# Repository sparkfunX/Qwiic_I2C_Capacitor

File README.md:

SparkFun Qwiic Digital Capacitor
=============================

[*SparkFun Qwiic Digital Capacitor NCD2400M (SPX- 17182)*](https://www.sparkfun.com/products/17182) 

Ever need to fine tune an oscillator circuit or RF filter? It can be tricky and repetitive switching out capacitors on a PCB. The Qwiic Digital Capacitor, complete with the NCD2400M IC, can be a great solution. Solder the nibs onto any 0603 or 0402 footprint, plug in a Qwiic cable and RedBoard, and change the capacitance in code.

Repository Contents
-------------------

* **/Documents** - Datasheet for the NCD2400M IC.
* **/Hardware** - Eagle design files (.brd, .sch).
* **/Production** - Production panel files (.brd).

Documentation
-------------
* **[Arduino Library](https://github.com/sparkfun/SparkFun_Qwiic_Digital_Capacitor_Arduino_Library)** - Arduino library for the SparkFun Qwiic Digital Capacitor - NCD2400M.

License Information
-------------------

This product is _**open source**_!

Please review the LICENSE.md file for license information.

If you have any questions or concerns regarding our licensing, please contact technical support on our [SparkFun Forum](https://www.sparkfun.com/viewforum.php?f=152).

Distributed as-is; no warranty is given.

- Your friends at SparkFun

_<COLLABORATION CREDIT>_

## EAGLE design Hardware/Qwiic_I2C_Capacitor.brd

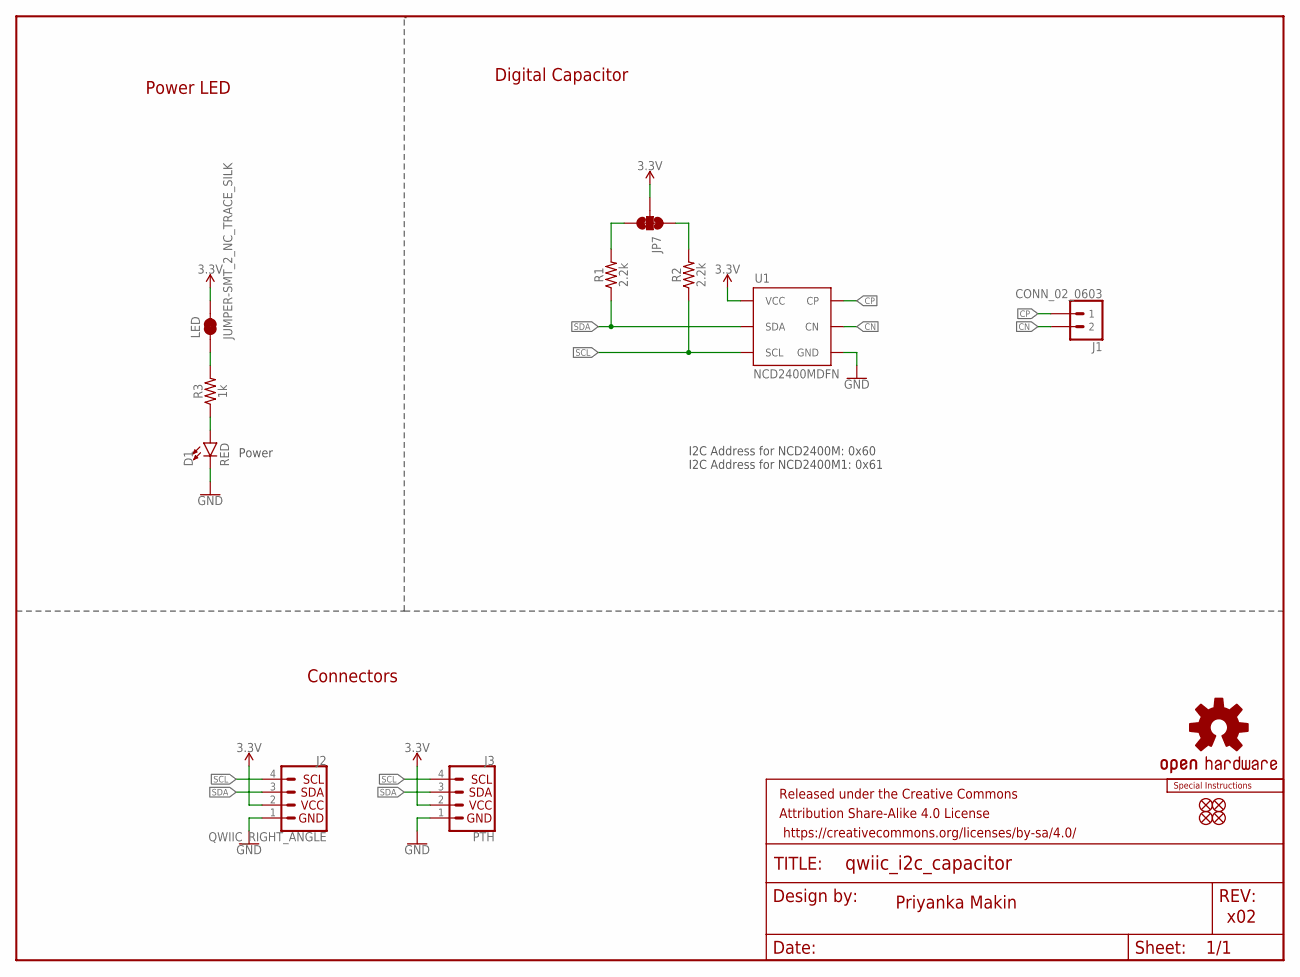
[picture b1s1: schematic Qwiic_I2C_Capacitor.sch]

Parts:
D1: RED; LED-0603
FRAME1: FRAME-LETTER; CREATIVE_COMMONS
J1: CONN_02_0603; 0603_CASTELLATED
J2: QWIIC_RIGHT_ANGLE; JST04_1MM_RA
J3: PTH; 1X04_NO_SILK
JP1, JP2, JP5, JP6: FIDUCIAL0.2MM; FIDUCIAL-0.2MM
JP7: JUMPER-SMT_3_2-NC_TRACE_SILK; SMT-JUMPER_3_2-NC_TRACE_SILK
LED: JUMPER-SMT_2_NC_TRACE_SILK; SMT-JUMPER_2_NC_TRACE_SILK
LOGO1: OSHW-LOGOMINI; OSHW-LOGO-MINI
LOGO2: SPECIAL_INSTRUCTIONS-ORDERING; ORDERING_INSTRUCTIONS
R1, R2: 2.2k; 0603
R3: 1k; 0603
U1: NCD2400MDFN; DFN6

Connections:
3.3V: J2.2, J3.2 (VCC), JP7.2, LED.2, U1.4 (VCC)
CN: J1.2, U1.3 (CN)
CP: J1.1, U1.2 (CP)
GND: D1.C, J2.1, J3.1 (GND), U1.5 (GND)
unnamed: JP7.3, R1.2
unnamed: JP7.1, R2.2
unnamed: D1.A, R3.1
unnamed: LED.1, R3.2
SCL: J2.4, J3.4 (SCL), R2.1, U1.6 (SCL)
SDA: J2.3, J3.3 (SDA), R1.1, U1.1 (SDA)

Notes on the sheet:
x02
Power
Connectors
Priyanka Makin
I2C Address for NCD2400M: 0x60 I2C Address for NCD2400M1: 0x61
Digital Capacitor
Power LED

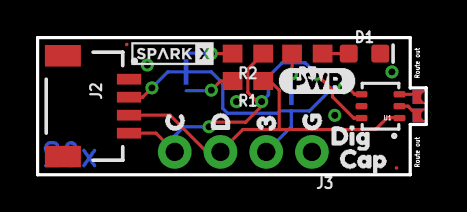
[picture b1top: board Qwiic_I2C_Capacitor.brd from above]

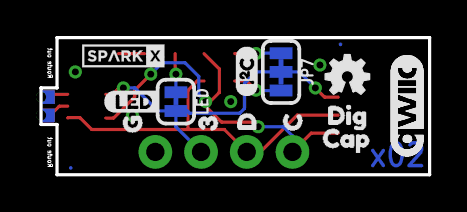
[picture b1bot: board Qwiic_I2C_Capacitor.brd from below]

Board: 2 copper layers, 21.6 x 7.6 mm, 36 parts (16 on the bottom side), 10 nets.

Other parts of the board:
U$1: PWR2
U$3, U$7: 32
U$4, U$8: C0
U$5, U$13: D1
U$6, U$14: G3
U$9: I_SUPER2_C-()-03
U$11, U$18: CAP1
U$12, U$16: SPARKX-TINY
U$15: LED0
U$20, U$21: QWIIC_COPYRIGHT_SMALL
U$22, U$23: DIG0

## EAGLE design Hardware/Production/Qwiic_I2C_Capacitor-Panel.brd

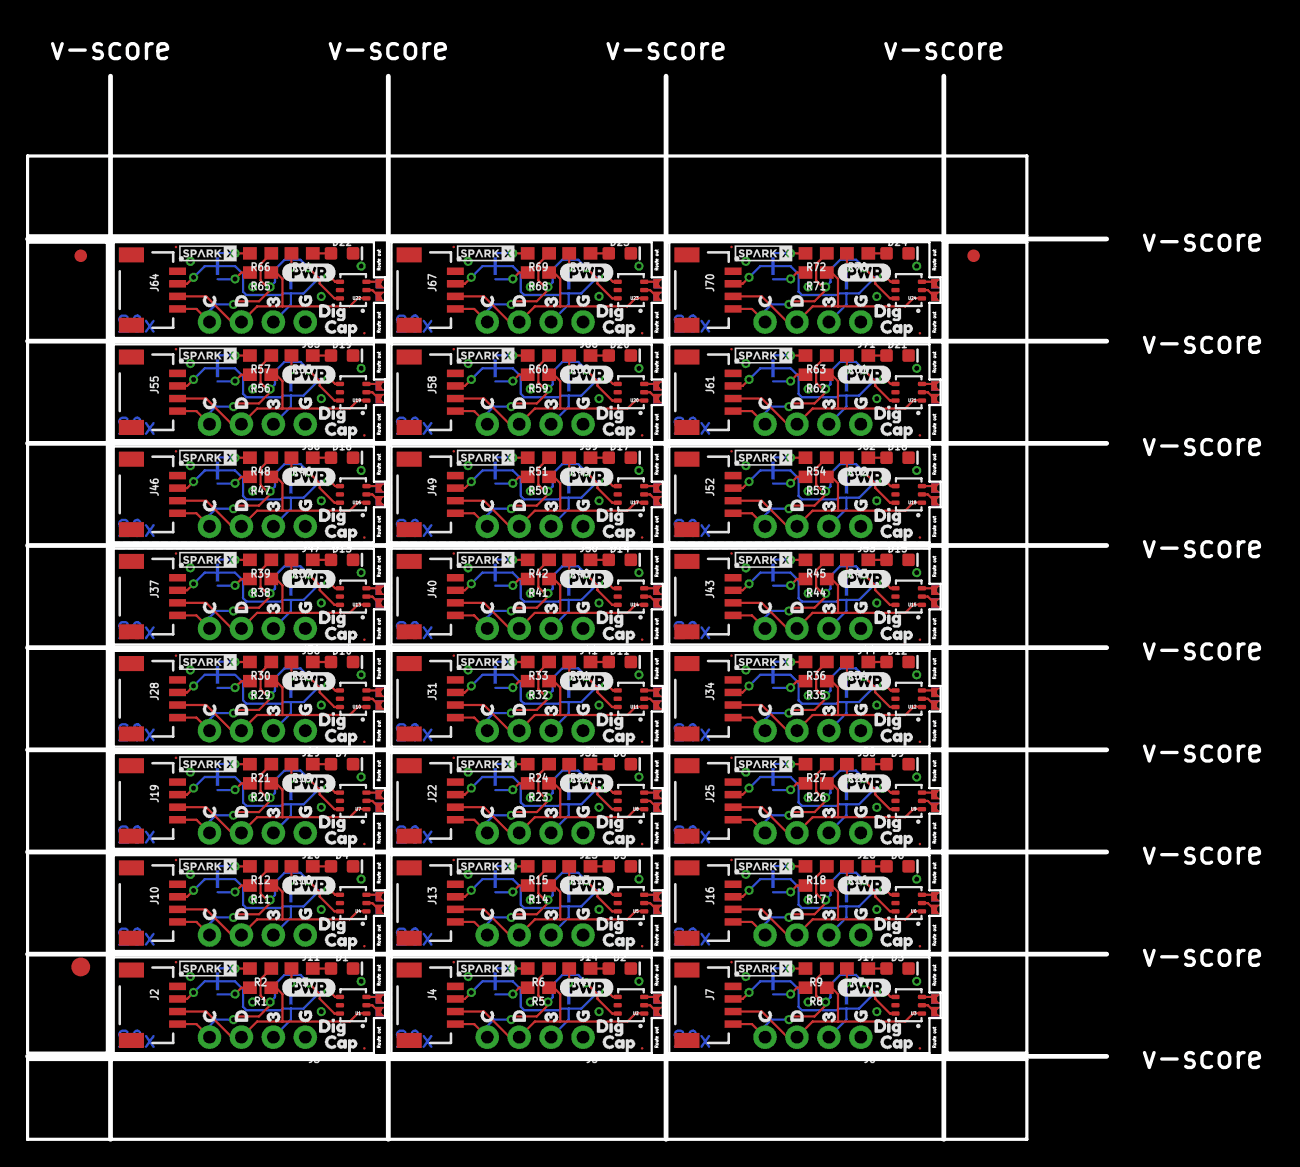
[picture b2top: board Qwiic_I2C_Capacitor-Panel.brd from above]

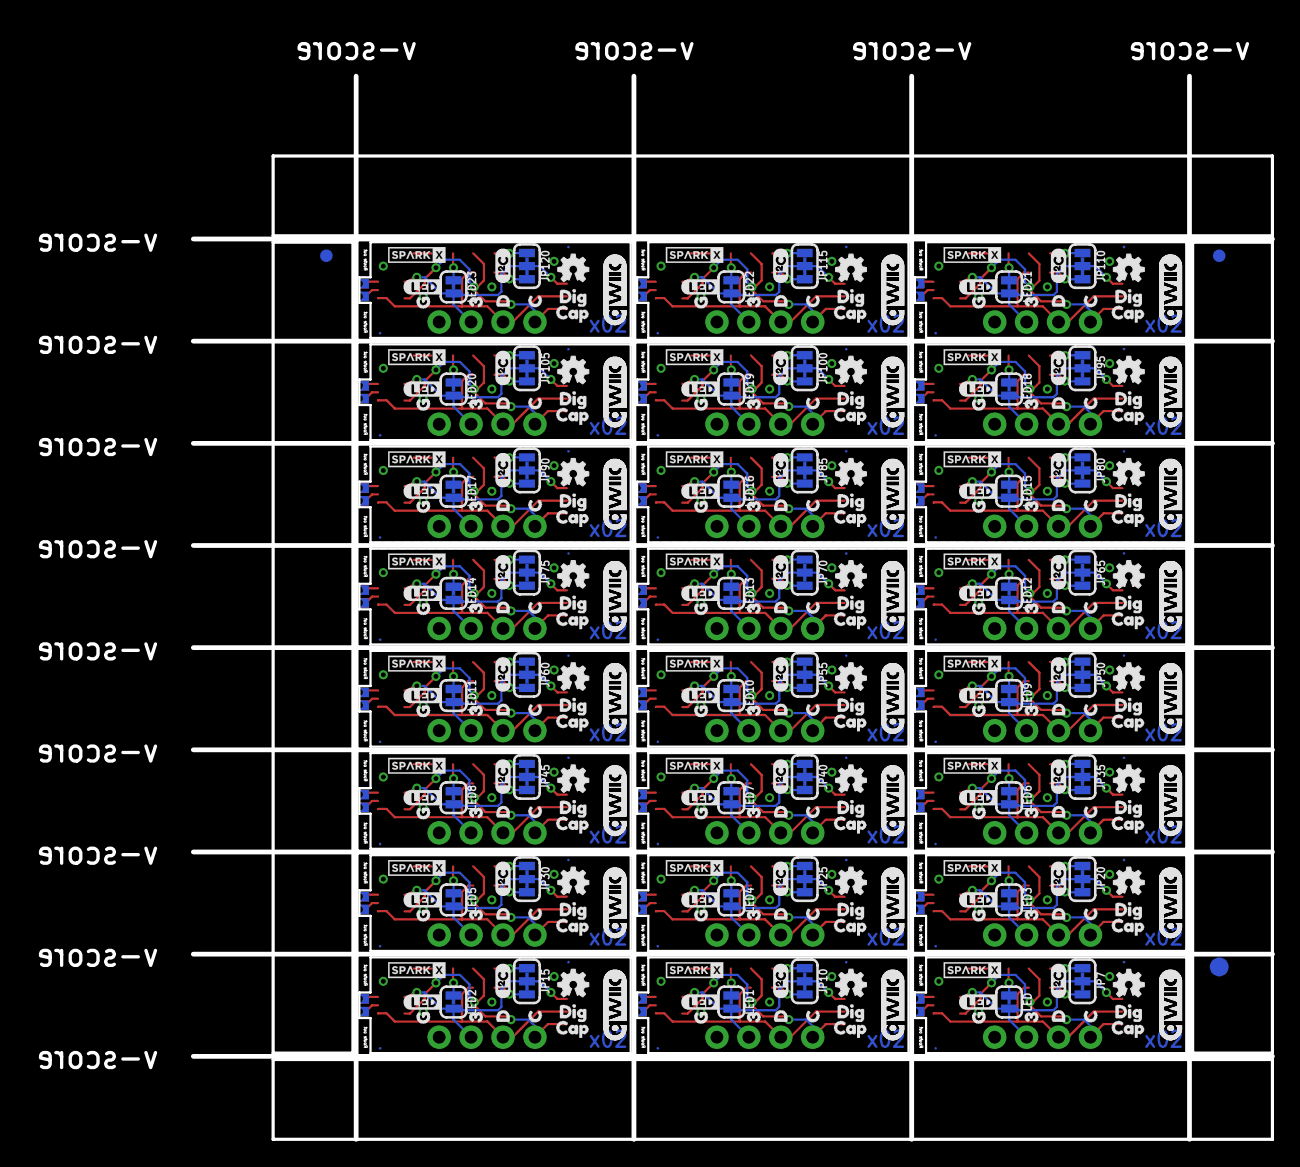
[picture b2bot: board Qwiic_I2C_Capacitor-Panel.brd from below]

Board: 2 copper layers, 99.0 x 88.5 mm, 822 parts (387 on the bottom side), 240 nets.

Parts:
D1, D2, D3, D4, D5, D6, D7, D8, D9, D10, D11, D12, D13, D14, D15, D16, D17, D18, D19, D20, D21, D22, D23, D24: RED; LED-0603
E$1, E$2, E$3, E$4: FIDUCIAL-1X2
E$5, E$6: FIDUCIAL-1.5X3
J1, J6, J9, J12, J15, J18, J21, J24, J27, J30, J33, J36, J39, J42, J45, J48, J51, J54, J57, J60, J63, J66, J69, J72: CONN_02_0603; 0603_CASTELLATED
J2, J4, J7, J10, J13, J16, J19, J22, J25, J28, J31, J34, J37, J40, J43, J46, J49, J52, J55, J58, J61, J64, J67, J70: QWIIC_RIGHT_ANGLE; JST04_1MM_RA
J3, J5, J8, J11, J14, J17, J20, J23, J26, J29, J32, J35, J38, J41, J44, J47, J50, J53, J56, J59, J62, J65, J68, J71: PTH; 1X04_NO_SILK
JP1, JP2, JP3, JP4, JP5, JP6, JP8, JP9, JP11, JP12, JP13, JP14, JP16, JP17, JP18, JP19, JP21, JP22, JP23, JP24, JP26, JP27, JP28, JP29, JP31, JP32, JP33, JP34, JP36, JP37, JP38, JP39, JP41, JP42, JP43, JP44, JP46, JP47, JP48, JP49, JP51, JP52, JP53, JP54, JP56, JP57, JP58, JP59, JP61, JP62, JP63, JP64, JP66, JP67, JP68, JP69, JP71, JP72, JP73, JP74, JP76, JP77, JP78, JP79, JP81, JP82, JP83, JP84, JP86, JP87, JP88, JP89, JP91, JP92, JP93, JP94, JP96, JP97, JP98, JP99, JP101, JP102, JP103, JP104, JP106, JP107, JP108, JP109, JP111, JP112, JP113, JP114, JP116, JP117, JP118, JP119: FIDUCIAL0.2MM; FIDUCIAL-0.2MM
JP7, JP10, JP15, JP20, JP25, JP30, JP35, JP40, JP45, JP50, JP55, JP60, JP65, JP70, JP75, JP80, JP85, JP90, JP95, JP100, JP105, JP110, JP115, JP120: JUMPER-SMT_3_2-NC_TRACE_SILK; SMT-JUMPER_3_2-NC_TRACE_SILK
LED, LED1, LED2, LED3, LED4, LED5, LED6, LED7, LED8, LED9, LED10, LED11, LED12, LED13, LED14, LED15, LED16, LED17, LED18, LED19, LED20, LED21, LED22, LED23: JUMPER-SMT_2_NC_TRACE_SILK; SMT-JUMPER_2_NC_TRACE_SILK
LOGO1, LOGO2, LOGO3, LOGO4, LOGO5, LOGO6, LOGO7, LOGO8, LOGO9, LOGO10, LOGO11, LOGO12, LOGO13, LOGO14, LOGO15, LOGO16, LOGO17, LOGO18, LOGO19, LOGO20, LOGO21, LOGO22, LOGO23, LOGO24: OSHW-LOGOMINI; OSHW-LOGO-MINI
R1, R2, R5, R6, R8, R9, R11, R12, R14, R15, R17, R18, R20, R21, R23, R24, R26, R27, R29, R30, R32, R33, R35, R36, R38, R39, R41, R42, R44, R45, R47, R48, R50, R51, R53, R54, R56, R57, R59, R60, R62, R63, R65, R66, R68, R69, R71, R72: 2.2k; 0603
R3, R4, R7, R10, R13, R16, R19, R22, R25, R28, R31, R34, R37, R40, R43, R46, R49, R52, R55, R58, R61, R64, R67, R70: 1k; 0603
U1, U2, U3, U4, U5, U6, U7, U8, U9, U10, U11, U12, U13, U14, U15, U16, U17, U18, U19, U20, U21, U22, U23, U24: NCD2400MDFN; DFN6
U$1, U$38, U$57, U$76, U$95, U$114, U$133, U$152, U$171, U$190, U$209, U$228, U$247, U$266, U$285, U$304, U$323, U$342, U$361, U$380, U$399, U$418, U$437, U$456: PWR2
U$2, U$9, U$39, U$58, U$77, U$96, U$115, U$134, U$153, U$172, U$191, U$210, U$229, U$248, U$267, U$286, U$305, U$324, U$343, U$362, U$381, U$400, U$419, U$438: I_SUPER2_C-()-03
U$3, U$7, U$10, U$25, U$40, U$44, U$59, U$63, U$78, U$82, U$97, U$101, U$116, U$120, U$135, U$139, U$154, U$158, U$173, U$177, U$192, U$196, U$211, U$215, U$230, U$234, U$249, U$253, U$268, U$272, U$287, U$291, U$306, U$310, U$325, U$329, U$344, U$348, U$363, U$367, U$382, U$386, U$401, U$405, U$420, U$424, U$439, U$443: 32
U$4, U$8, U$17, U$26, U$41, U$45, U$60, U$64, U$79, U$83, U$98, U$102, U$117, U$121, U$136, U$140, U$155, U$159, U$174, U$178, U$193, U$197, U$212, U$216, U$231, U$235, U$250, U$254, U$269, U$273, U$288, U$292, U$307, U$311, U$326, U$330, U$345, U$349, U$364, U$368, U$383, U$387, U$402, U$406, U$421, U$425, U$440, U$444: C0
U$5, U$13, U$19, U$27, U$42, U$46, U$61, U$65, U$80, U$84, U$99, U$103, U$118, U$122, U$137, U$141, U$156, U$160, U$175, U$179, U$194, U$198, U$213, U$217, U$232, U$236, U$251, U$255, U$270, U$274, U$289, U$293, U$308, U$312, U$327, U$331, U$346, U$350, U$365, U$369, U$384, U$388, U$403, U$407, U$422, U$426, U$441, U$445: D1
U$6, U$14, U$24, U$28, U$43, U$47, U$62, U$66, U$81, U$85, U$100, U$104, U$119, U$123, U$138, U$142, U$157, U$161, U$176, U$180, U$195, U$199, U$214, U$218, U$233, U$237, U$252, U$256, U$271, U$275, U$290, U$294, U$309, U$313, U$328, U$332, U$347, U$351, U$366, U$370, U$385, U$389, U$404, U$408, U$423, U$427, U$442, U$446: G3
U$11, U$18, U$34, U$35, U$53, U$54, U$72, U$73, U$91, U$92, U$110, U$111, U$129, U$130, U$148, U$149, U$167, U$168, U$186, U$187, U$205, U$206, U$224, U$225, U$243, U$244, U$262, U$263, U$281, U$282, U$300, U$301, U$319, U$320, U$338, U$339, U$357, U$358, U$376, U$377, U$395, U$396, U$414, U$415, U$433, U$434, U$452, U$453: CAP1
U$12, U$16, U$30, U$31, U$49, U$50, U$68, U$69, U$87, U$88, U$106, U$107, U$125, U$126, U$144, U$145, U$163, U$164, U$182, U$183, U$201, U$202, U$220, U$221, U$239, U$240, U$258, U$259, U$277, U$278, U$296, U$297, U$315, U$316, U$334, U$335, U$353, U$354, U$372, U$373, U$391, U$392, U$410, U$411, U$429, U$430, U$448, U$449: SPARKX-TINY
U$15, U$29, U$48, U$67, U$86, U$105, U$124, U$143, U$162, U$181, U$200, U$219, U$238, U$257, U$276, U$295, U$314, U$333, U$352, U$371, U$390, U$409, U$428, U$447: LED0
U$20, U$21, U$32, U$33, U$51, U$52, U$70, U$71, U$89, U$90, U$108, U$109, U$127, U$128, U$146, U$147, U$165, U$166, U$184, U$185, U$203, U$204, U$222, U$223, U$241, U$242, U$260, U$261, U$279, U$280, U$298, U$299, U$317, U$318, U$336, U$337, U$355, U$356, U$374, U$375, U$393, U$394, U$412, U$413, U$431, U$432, U$450, U$451: QWIIC_COPYRIGHT_SMALL
U$22, U$23, U$36, U$37, U$55, U$56, U$74, U$75, U$93, U$94, U$112, U$113, U$131, U$132, U$150, U$151, U$169, U$170, U$188, U$189, U$207, U$208, U$226, U$227, U$245, U$246, U$264, U$265, U$283, U$284, U$302, U$303, U$321, U$322, U$340, U$341, U$359, U$360, U$378, U$379, U$397, U$398, U$416, U$417, U$435, U$436, U$454, U$455: DIG0

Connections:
3.3V: J2.2, J3.2, JP7.2, LED.2, U1.4
3.3V1: J4.2, J5.2, JP10.2, LED1.2, U2.4
3.3V2: J7.2, J8.2, JP15.2, LED2.2, U3.4
3.3V3: J10.2, J11.2, JP20.2, LED3.2, U4.4
3.3V4: J13.2, J14.2, JP25.2, LED4.2, U5.4
3.3V5: J16.2, J17.2, JP30.2, LED5.2, U6.4
3.3V6: J19.2, J20.2, JP35.2, LED6.2, U7.4
3.3V7: J22.2, J23.2, JP40.2, LED7.2, U8.4
3.3V8: J25.2, J26.2, JP45.2, LED8.2, U9.4
3.3V9: J28.2, J29.2, JP50.2, LED9.2, U10.4
3.3V10: J31.2, J32.2, JP55.2, LED10.2, U11.4
3.3V11: J34.2, J35.2, JP60.2, LED11.2, U12.4
3.3V12: J37.2, J38.2, JP65.2, LED12.2, U13.4
3.3V13: J40.2, J41.2, JP70.2, LED13.2, U14.4
3.3V14: J43.2, J44.2, JP75.2, LED14.2, U15.4
3.3V15: J46.2, J47.2, JP80.2, LED15.2, U16.4
3.3V16: J49.2, J50.2, JP85.2, LED16.2, U17.4
3.3V17: J52.2, J53.2, JP90.2, LED17.2, U18.4
3.3V18: J55.2, J56.2, JP95.2, LED18.2, U19.4
3.3V19: J58.2, J59.2, JP100.2, LED19.2, U20.4
3.3V20: J61.2, J62.2, JP105.2, LED20.2, U21.4
3.3V21: J64.2, J65.2, JP110.2, LED21.2, U22.4
3.3V22: J67.2, J68.2, JP115.2, LED22.2, U23.4
3.3V23: J70.2, J71.2, JP120.2, LED23.2, U24.4
CN: J1.2, U1.3
CN1: J6.2, U2.3
CN2: J9.2, U3.3
CN3: J12.2, U4.3
CN4: J15.2, U5.3
CN5: J18.2, U6.3
CN6: J21.2, U7.3
CN7: J24.2, U8.3
CN8: J27.2, U9.3
CN9: J30.2, U10.3
CN10: J33.2, U11.3
CN11: J36.2, U12.3
CN12: J39.2, U13.3
CN13: J42.2, U14.3
CN14: J45.2, U15.3
CN15: J48.2, U16.3
CN16: J51.2, U17.3
CN17: J54.2, U18.3
CN18: J57.2, U19.3
CN19: J60.2, U20.3
CN20: J63.2, U21.3
CN21: J66.2, U22.3
CN22: J69.2, U23.3
CN23: J72.2, U24.3
CP: J1.1, U1.2
CP1: J6.1, U2.2
CP2: J9.1, U3.2
CP3: J12.1, U4.2
CP4: J15.1, U5.2
CP5: J18.1, U6.2
CP6: J21.1, U7.2
CP7: J24.1, U8.2
CP8: J27.1, U9.2
CP9: J30.1, U10.2
CP10: J33.1, U11.2
CP11: J36.1, U12.2
CP12: J39.1, U13.2
CP13: J42.1, U14.2
CP14: J45.1, U15.2
CP15: J48.1, U16.2
CP16: J51.1, U17.2
CP17: J54.1, U18.2
CP18: J57.1, U19.2
CP19: J60.1, U20.2
CP20: J63.1, U21.2
CP21: J66.1, U22.2
CP22: J69.1, U23.2
CP23: J72.1, U24.2
GND: D1.C, J2.1, J3.1, U1.5
GND1: D2.C, J4.1, J5.1, U2.5
GND2: D3.C, J7.1, J8.1, U3.5
GND3: D4.C, J10.1, J11.1, U4.5
GND4: D5.C, J13.1, J14.1, U5.5
GND5: D6.C, J16.1, J17.1, U6.5
GND6: D7.C, J19.1, J20.1, U7.5
GND7: D8.C, J22.1, J23.1, U8.5
GND8: D9.C, J25.1, J26.1, U9.5
GND9: D10.C, J28.1, J29.1, U10.5
GND10: D11.C, J31.1, J32.1, U11.5
GND11: D12.C, J34.1, J35.1, U12.5
GND12: D13.C, J37.1, J38.1, U13.5
GND13: D14.C, J40.1, J41.1, U14.5
GND14: D15.C, J43.1, J44.1, U15.5
GND15: D16.C, J46.1, J47.1, U16.5
GND16: D17.C, J49.1, J50.1, U17.5
GND17: D18.C, J52.1, J53.1, U18.5
GND18: D19.C, J55.1, J56.1, U19.5
GND19: D20.C, J58.1, J59.1, U20.5
GND20: D21.C, J61.1, J62.1, U21.5
GND21: D22.C, J64.1, J65.1, U22.5
GND22: D23.C, J67.1, J68.1, U23.5
GND23: D24.C, J70.1, J71.1, U24.5
unnamed: JP7.3, R1.2
unnamed: JP7.1, R2.2
unnamed: D1.A, R3.1
unnamed: LED.1, R3.2
unnamed: D2.A, R4.1
unnamed: JP10.3, R5.2
unnamed: JP10.1, R6.2
unnamed: LED1.1, R4.2
unnamed: D3.A, R7.1
unnamed: JP15.3, R8.2
unnamed: JP15.1, R9.2
unnamed: LED2.1, R7.2
unnamed: D4.A, R10.1
unnamed: JP20.3, R11.2
unnamed: JP20.1, R12.2
unnamed: LED3.1, R10.2
unnamed: D5.A, R13.1
unnamed: JP25.3, R14.2
unnamed: JP25.1, R15.2
unnamed: LED4.1, R13.2
unnamed: D6.A, R16.1
unnamed: JP30.3, R17.2
unnamed: JP30.1, R18.2
unnamed: LED5.1, R16.2
unnamed: D7.A, R19.1
unnamed: JP35.3, R20.2
unnamed: JP35.1, R21.2
unnamed: LED6.1, R19.2
unnamed: D8.A, R22.1
unnamed: JP40.3, R23.2
unnamed: JP40.1, R24.2
unnamed: LED7.1, R22.2
unnamed: D9.A, R25.1
unnamed: JP45.3, R26.2
unnamed: JP45.1, R27.2
unnamed: LED8.1, R25.2
unnamed: D10.A, R28.1
unnamed: JP50.3, R29.2
unnamed: JP50.1, R30.2
unnamed: LED9.1, R28.2
unnamed: D11.A, R31.1
unnamed: JP55.3, R32.2
unnamed: JP55.1, R33.2
unnamed: LED10.1, R31.2
unnamed: D12.A, R34.1
unnamed: JP60.3, R35.2
unnamed: JP60.1, R36.2
unnamed: LED11.1, R34.2
unnamed: D13.A, R37.1
unnamed: JP65.3, R38.2
unnamed: JP65.1, R39.2
unnamed: LED12.1, R37.2
unnamed: D14.A, R40.1
unnamed: JP70.3, R41.2
unnamed: JP70.1, R42.2
unnamed: LED13.1, R40.2
unnamed: D15.A, R43.1
unnamed: JP75.3, R44.2
unnamed: JP75.1, R45.2
unnamed: LED14.1, R43.2
unnamed: D16.A, R46.1
unnamed: JP80.3, R47.2
unnamed: JP80.1, R48.2
unnamed: LED15.1, R46.2
unnamed: D17.A, R49.1
unnamed: JP85.3, R50.2
unnamed: JP85.1, R51.2
unnamed: LED16.1, R49.2
unnamed: D18.A, R52.1
unnamed: JP90.3, R53.2
unnamed: JP90.1, R54.2
unnamed: LED17.1, R52.2
unnamed: D19.A, R55.1
unnamed: JP95.3, R56.2
unnamed: JP95.1, R57.2
unnamed: LED18.1, R55.2
unnamed: D20.A, R58.1
unnamed: JP100.3, R59.2
unnamed: JP100.1, R60.2
unnamed: LED19.1, R58.2
unnamed: D21.A, R61.1
unnamed: JP105.3, R62.2
unnamed: JP105.1, R63.2
unnamed: LED20.1, R61.2
unnamed: D22.A, R64.1
unnamed: JP110.3, R65.2
unnamed: JP110.1, R66.2
unnamed: LED21.1, R64.2
unnamed: D23.A, R67.1
unnamed: JP115.3, R68.2
unnamed: JP115.1, R69.2
unnamed: LED22.1, R67.2
unnamed: D24.A, R70.1
unnamed: JP120.3, R71.2
unnamed: JP120.1, R72.2
unnamed: LED23.1, R70.2
SCL: J2.4, J3.4, R2.1, U1.6
SCL1: J4.4, J5.4, R6.1, U2.6
SCL2: J7.4, J8.4, R9.1, U3.6
SCL3: J10.4, J11.4, R12.1, U4.6
SCL4: J13.4, J14.4, R15.1, U5.6
SCL5: J16.4, J17.4, R18.1, U6.6
SCL6: J19.4, J20.4, R21.1, U7.6
SCL7: J22.4, J23.4, R24.1, U8.6
SCL8: J25.4, J26.4, R27.1, U9.6
SCL9: J28.4, J29.4, R30.1, U10.6
SCL10: J31.4, J32.4, R33.1, U11.6
SCL11: J34.4, J35.4, R36.1, U12.6
SCL12: J37.4, J38.4, R39.1, U13.6
SCL13: J40.4, J41.4, R42.1, U14.6
SCL14: J43.4, J44.4, R45.1, U15.6
SCL15: J46.4, J47.4, R48.1, U16.6
SCL16: J49.4, J50.4, R51.1, U17.6
SCL17: J52.4, J53.4, R54.1, U18.6
SCL18: J55.4, J56.4, R57.1, U19.6
SCL19: J58.4, J59.4, R60.1, U20.6
SCL20: J61.4, J62.4, R63.1, U21.6
SCL21: J64.4, J65.4, R66.1, U22.6
SCL22: J67.4, J68.4, R69.1, U23.6
SCL23: J70.4, J71.4, R72.1, U24.6
SDA: J2.3, J3.3, R1.1, U1.1
SDA1: J4.3, J5.3, R5.1, U2.1
SDA2: J7.3, J8.3, R8.1, U3.1
SDA3: J10.3, J11.3, R11.1, U4.1
SDA4: J13.3, J14.3, R14.1, U5.1
SDA5: J16.3, J17.3, R17.1, U6.1
SDA6: J19.3, J20.3, R20.1, U7.1
SDA7: J22.3, J23.3, R23.1, U8.1
SDA8: J25.3, J26.3, R26.1, U9.1
SDA9: J28.3, J29.3, R29.1, U10.1
SDA10: J31.3, J32.3, R32.1, U11.1
SDA11: J34.3, J35.3, R35.1, U12.1
SDA12: J37.3, J38.3, R38.1, U13.1
SDA13: J40.3, J41.3, R41.1, U14.1
SDA14: J43.3, J44.3, R44.1, U15.1
SDA15: J46.3, J47.3, R47.1, U16.1
SDA16: J49.3, J50.3, R50.1, U17.1
SDA17: J52.3, J53.3, R53.1, U18.1
SDA18: J55.3, J56.3, R56.1, U19.1
SDA19: J58.3, J59.3, R59.1, U20.1
SDA20: J61.3, J62.3, R62.1, U21.1
SDA21: J64.3, J65.3, R65.1, U22.1
SDA22: J67.3, J68.3, R68.1, U23.1
SDA23: J70.3, J71.3, R71.1, U24.1

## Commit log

2020-08-24 Added NCD2400M to schematic
2020-08-24 Renamed eagle files
2020-08-27 Initial layout
2020-08-27 Changes from board review
2020-08-27 Panelizer/cam output
2020-10-06 Rev x02
    Re-routed SDA and SCL. They were backwards in the previous version x01
2020-10-13 Writing examples
2020-10-20 Generate product page files
2020-11-20 Update README.md
    Added info
2020-11-20 Update README.md
    added picture to README
2020-11-20 Create License.md
    added license

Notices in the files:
parts and their libraries:
SparkFun-Resistors: Licensing: Creative Commons ShareAlike 4.0 International - https://creativecommons.org/licenses/by-sa/4.0
SparkFun-Aesthetics: Released under the Creative Commons Attribution Share-Alike 4.0 License
SparkFun-Aesthetics: https://creativecommons.org/licenses/by-sa/4.0
